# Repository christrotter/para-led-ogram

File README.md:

# para-led-ogram

- reversible for each split half
- paralellogram shape for more fun
- 16 RGB leds
- 4-pin 0.5mm-pitch 'top and bottom conductor' connector; pinout reversed for other half so you don't need to twist the FFC
- test pads

On the Arcboard mk22 I wanted the indicator bar to be a first-class RGB citizen, thus it got its own pcb.
Additionally, I wanted it to connect via FFC - and that required making it possible to plug in on both halves.

Future revisions will move to bottom-only conductors, and skip the reversed pinout - this created more confusion than it was worth.

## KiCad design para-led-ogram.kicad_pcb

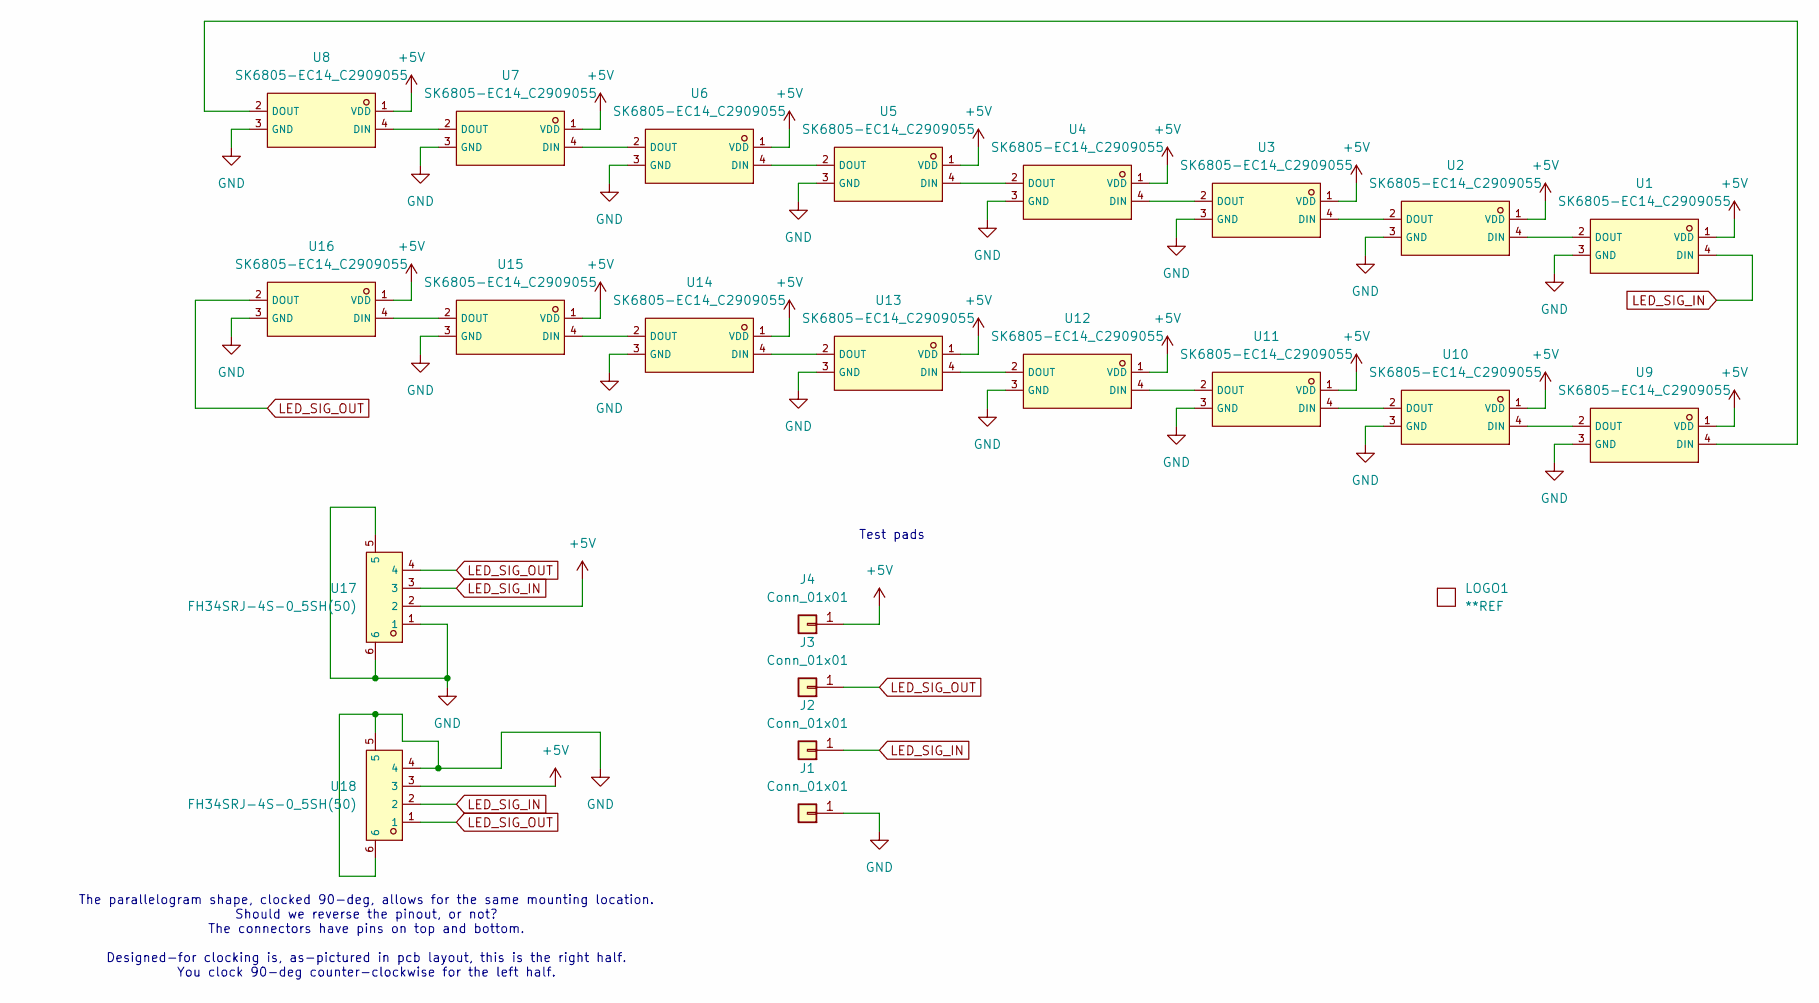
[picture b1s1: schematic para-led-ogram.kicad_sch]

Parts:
J1, J2, J3, J4: Conn_01x01; TestPoint_Pad_D1.0mm
LOGO1: **REF; awesome-logo
U1, U2, U3, U4, U5, U6, U7, U8, U9, U10, U11, U12, U13, U14, U15, U16: SK6805-EC14_C2909055; LED-SMD_4P-L1.4-W1.4-TL; LCSC C2909055
U17, U18: FH34SRJ-4S-0_5SH(50); FPC-SMD_FH34SRJ-4S-0.5SH-50; LCSC C596732

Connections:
+5V: J4.1, U1.1 (VDD), U2.1 (VDD), U3.1 (VDD), U4.1 (VDD), U5.1 (VDD), U6.1 (VDD), U7.1 (VDD), U8.1 (VDD), U9.1 (VDD), U10.1 (VDD), U11.1 (VDD), U12.1 (VDD), U13.1 (VDD), U14.1 (VDD), U15.1 (VDD), U16.1 (VDD), U17.2, U18.3
GND: J1.1, U1.3 (GND), U2.3 (GND), U3.3 (GND), U4.3 (GND), U5.3 (GND), U6.3 (GND), U7.3 (GND), U8.3 (GND), U9.3 (GND), U10.3 (GND), U11.3 (GND), U12.3 (GND), U13.3 (GND), U14.3 (GND), U15.3 (GND), U16.3 (GND), U17.1, U17.5, U17.6, U18.4, U18.5, U18.6
LED_SIG_IN: J2.1, U1.4 (DIN), U17.3, U18.2
LED_SIG_OUT: J3.1, U16.2 (DOUT), U17.4, U18.1
unnamed: U1.2 (DOUT), U2.4 (DIN)
unnamed: U2.2 (DOUT), U3.4 (DIN)
unnamed: U3.2 (DOUT), U4.4 (DIN)
unnamed: U4.2 (DOUT), U5.4 (DIN)
unnamed: U5.2 (DOUT), U6.4 (DIN)
unnamed: U6.2 (DOUT), U7.4 (DIN)
unnamed: U7.2 (DOUT), U8.4 (DIN)
unnamed: U8.2 (DOUT), U9.4 (DIN)
unnamed: U9.2 (DOUT), U10.4 (DIN)
unnamed: U10.2 (DOUT), U11.4 (DIN)
unnamed: U11.2 (DOUT), U12.4 (DIN)
unnamed: U12.2 (DOUT), U13.4 (DIN)
unnamed: U13.2 (DOUT), U14.4 (DIN)
unnamed: U14.2 (DOUT), U15.4 (DIN)
unnamed: U15.2 (DOUT), U16.4 (DIN)

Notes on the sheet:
Test pads
The parallelogram shape, clocked 90-deg, allows for the same mounting location. Should we reverse the pinout, or not? The connectors have pins on top and bottom. Designed-for clocking is, as-pictured in pcb layout, this is the right half. You clock 90-deg counter-clockwise for the left half.

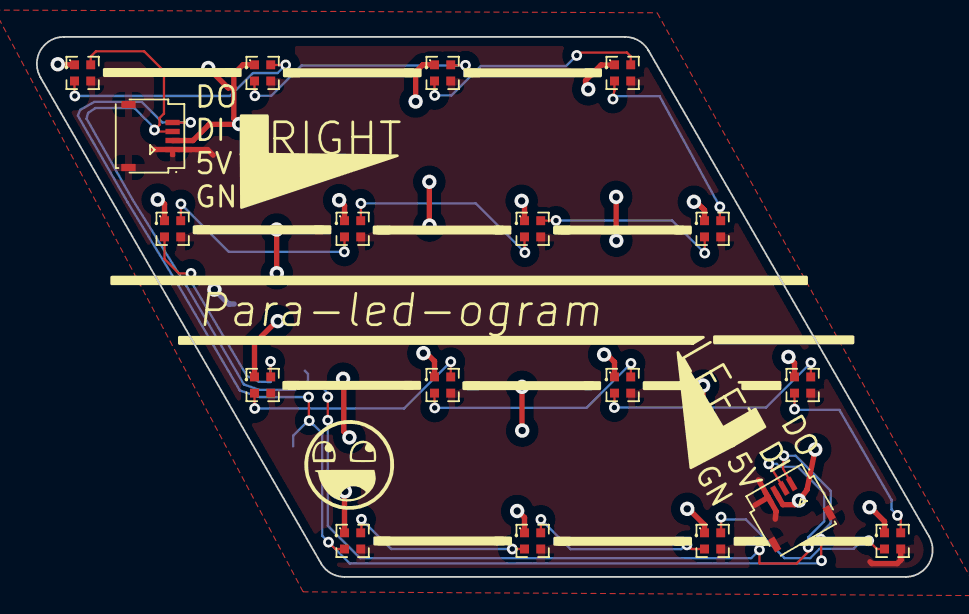
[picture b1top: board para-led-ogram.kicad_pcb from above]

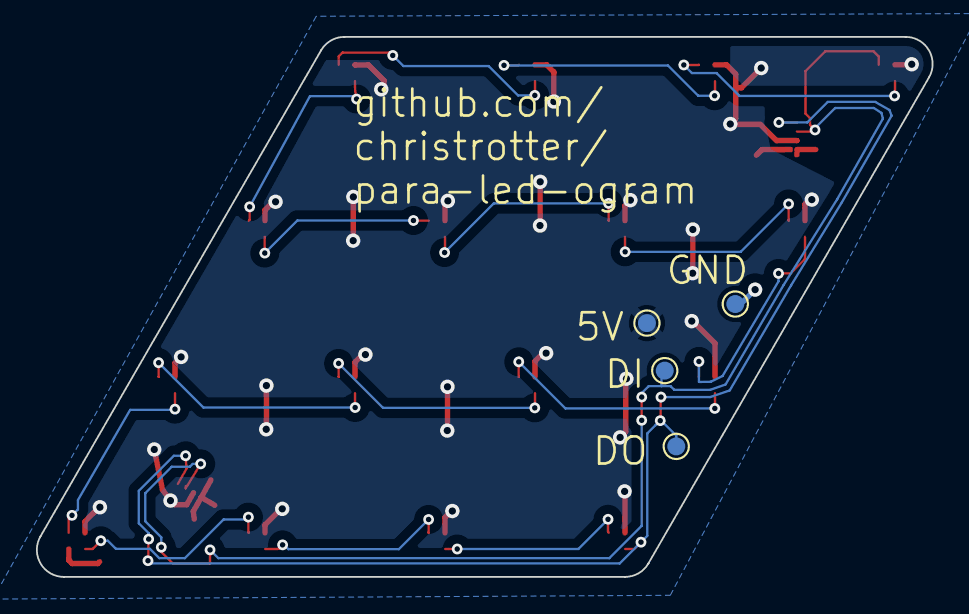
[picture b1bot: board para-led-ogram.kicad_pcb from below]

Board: 2 copper layers, 49.8 x 30.0 mm, 23 parts (4 on the bottom side), 19 nets.

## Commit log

2026-06-23 rev1 all dun
